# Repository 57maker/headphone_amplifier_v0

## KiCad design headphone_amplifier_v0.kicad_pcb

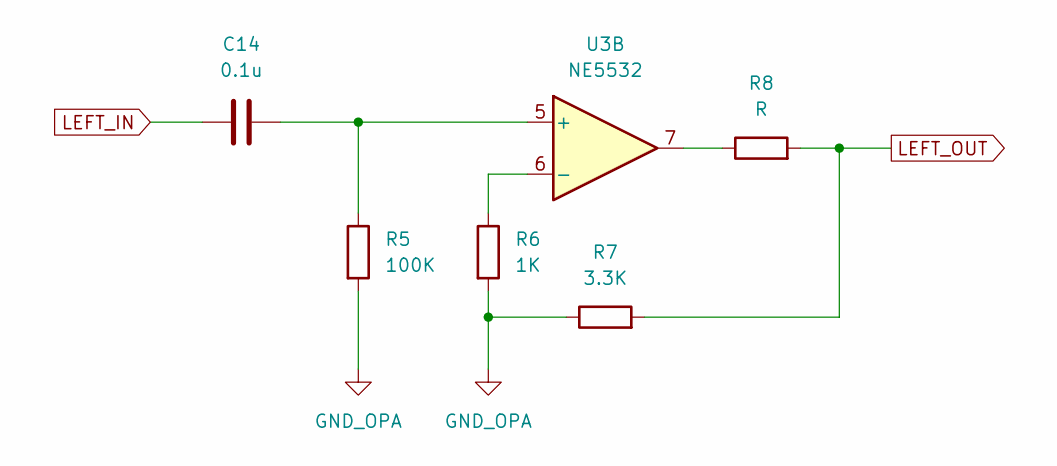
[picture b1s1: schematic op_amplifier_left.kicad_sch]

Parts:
C14: 0.1u; C_Rect_L10.0mm_W5.0mm_P5.00mm_P7.50mm
R5: 100K; R_Axial_DIN0309_L9.0mm_D3.2mm_P12.70mm_Horizontal
R6: 1K; R_Axial_DIN0309_L9.0mm_D3.2mm_P12.70mm_Horizontal
R7: 3.3K; R_Axial_DIN0309_L9.0mm_D3.2mm_P12.70mm_Horizontal
R8: R; R_Axial_DIN0309_L9.0mm_D3.2mm_P12.70mm_Horizontal
U3: NE5532; DIP-8_W7.62mm_Socket

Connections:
GND_OPA: R5.2, R6.2, R7.1; also elsewhere on the board
LEFT_IN: C14.1; also elsewhere on the board
LEFT_OUT: R7.2, R8.2; also elsewhere on the board
unnamed: R8.1, U3.7
unnamed: C14.2, R5.1, U3.5 (+)
unnamed: R6.1, U3.6 (-)

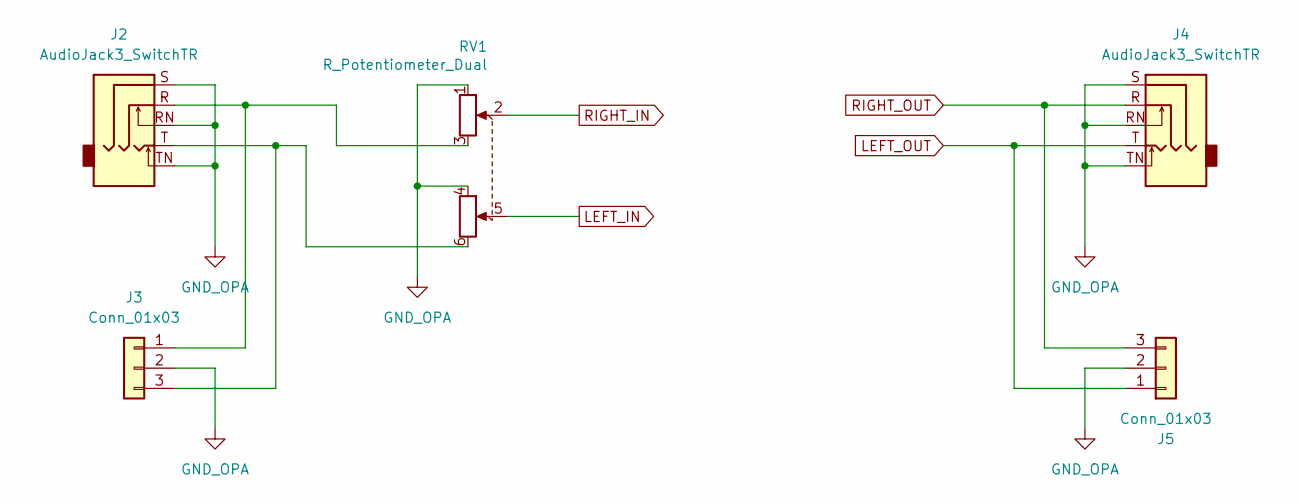
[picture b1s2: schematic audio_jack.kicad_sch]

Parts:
J2, J4: AudioJack3_SwitchTR; Jack_3.5mm_CUI_SJ1-3515N_Horizontal
J3, J5: Conn_01x03; TerminalBlock_TE_282834-3_1x03_P2.54mm_Horizontal
RV1: R_Potentiometer_Dual; Potentiometer_Alps_RK097_Dual_Horizontal

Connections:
GND_OPA: J2.RN, J2.S, J2.TN, J3.2, J4.RN, J4.S, J4.TN, J5.2, RV1.1, RV1.4; also elsewhere on the board
LEFT_IN: RV1.5; also elsewhere on the board
LEFT_OUT: J4.T, J5.1; also elsewhere on the board
unnamed: J2.R, J3.1, RV1.3
unnamed: J2.T, J3.3, RV1.6
RIGHT_IN: RV1.2; also elsewhere on the board
RIGHT_OUT: J4.R, J5.3; also elsewhere on the board

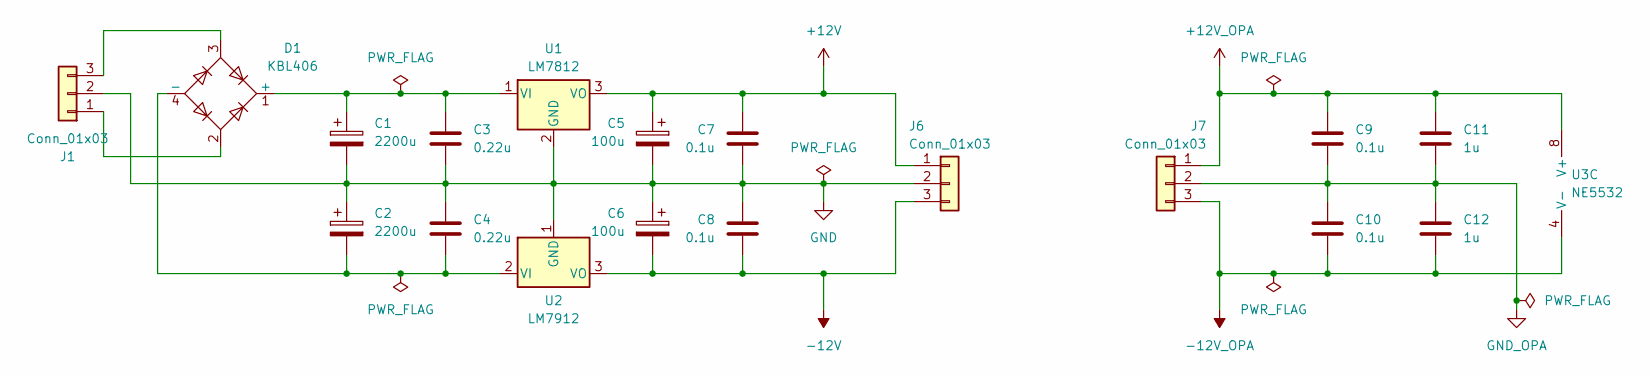
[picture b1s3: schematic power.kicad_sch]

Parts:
C1, C2: 2200u; CP_Radial_D12.5mm_P5.00mm
C3, C4: 0.22u; C_Disc_D5.0mm_W2.5mm_P5.00mm
C5, C6: 100u; CP_Radial_D5.0mm_P2.50mm
C7, C8, C9, C10: 0.1u; C_Disc_D5.0mm_W2.5mm_P5.00mm
C11, C12: 1u; C_Disc_D5.0mm_W2.5mm_P5.00mm
D1: KBL406; Diode_Bridge_Vishay_KBU
J1: Conn_01x03; TerminalBlock_TE_282834-3_1x03_P2.54mm_Horizontal
J6, J7: Conn_01x03; PinHeader_1x03_P2.54mm_Vertical
U1: LM7812; TO-220-3_Vertical
U2: LM7912; TO-220-3_Vertical
U3: NE5532; DIP-8_W7.62mm_Socket

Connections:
+12V: C5.1, C7.2, J6.1, U1.3 (VO)
+12V_OPA: C9.2, C11.2, J7.1, U3.8 (V+)
-12V: C6.2, C8.1, J6.3, U2.3 (VO)
-12V_OPA: C10.1, C12.1, J7.3, U3.4 (V-)
GND: C1.2, C2.1, C3.1, C4.2, C5.2, C6.1, C7.1, C8.2, J1.2, J6.2, U1.2 (GND), U2.1 (GND)
GND_OPA: C9.1, C10.2, C11.1, C12.2, J7.2; also elsewhere on the board
unnamed: C1.1, C3.2, D1.1 (+), U1.1 (VI)
unnamed: C2.2, C4.1, D1.4 (-), U2.2 (VI)
unnamed: D1.2, J1.1
unnamed: D1.3, J1.3

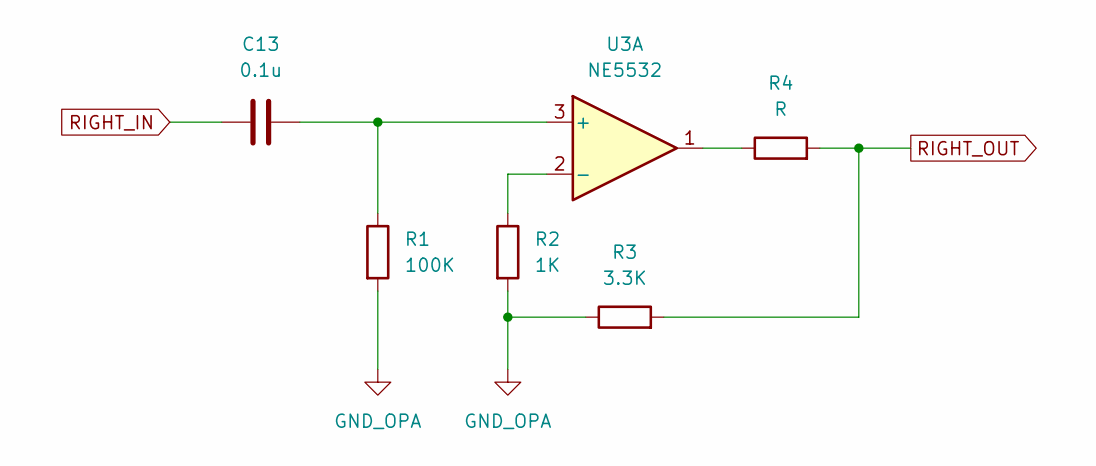
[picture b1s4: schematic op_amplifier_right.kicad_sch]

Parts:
C13: 0.1u; C_Rect_L10.0mm_W5.0mm_P5.00mm_P7.50mm
R1: 100K; R_Axial_DIN0309_L9.0mm_D3.2mm_P12.70mm_Horizontal
R2: 1K; R_Axial_DIN0309_L9.0mm_D3.2mm_P12.70mm_Horizontal
R3: 3.3K; R_Axial_DIN0309_L9.0mm_D3.2mm_P12.70mm_Horizontal
R4: R; R_Axial_DIN0309_L9.0mm_D3.2mm_P12.70mm_Horizontal
U3: NE5532; DIP-8_W7.62mm_Socket

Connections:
GND_OPA: R1.2, R2.2, R3.1; also elsewhere on the board
unnamed: R4.1, U3.1
unnamed: C13.2, R1.1, U3.3 (+)
unnamed: R2.1, U3.2 (-)
RIGHT_IN: C13.1; also elsewhere on the board
RIGHT_OUT: R3.2, R4.2; also elsewhere on the board

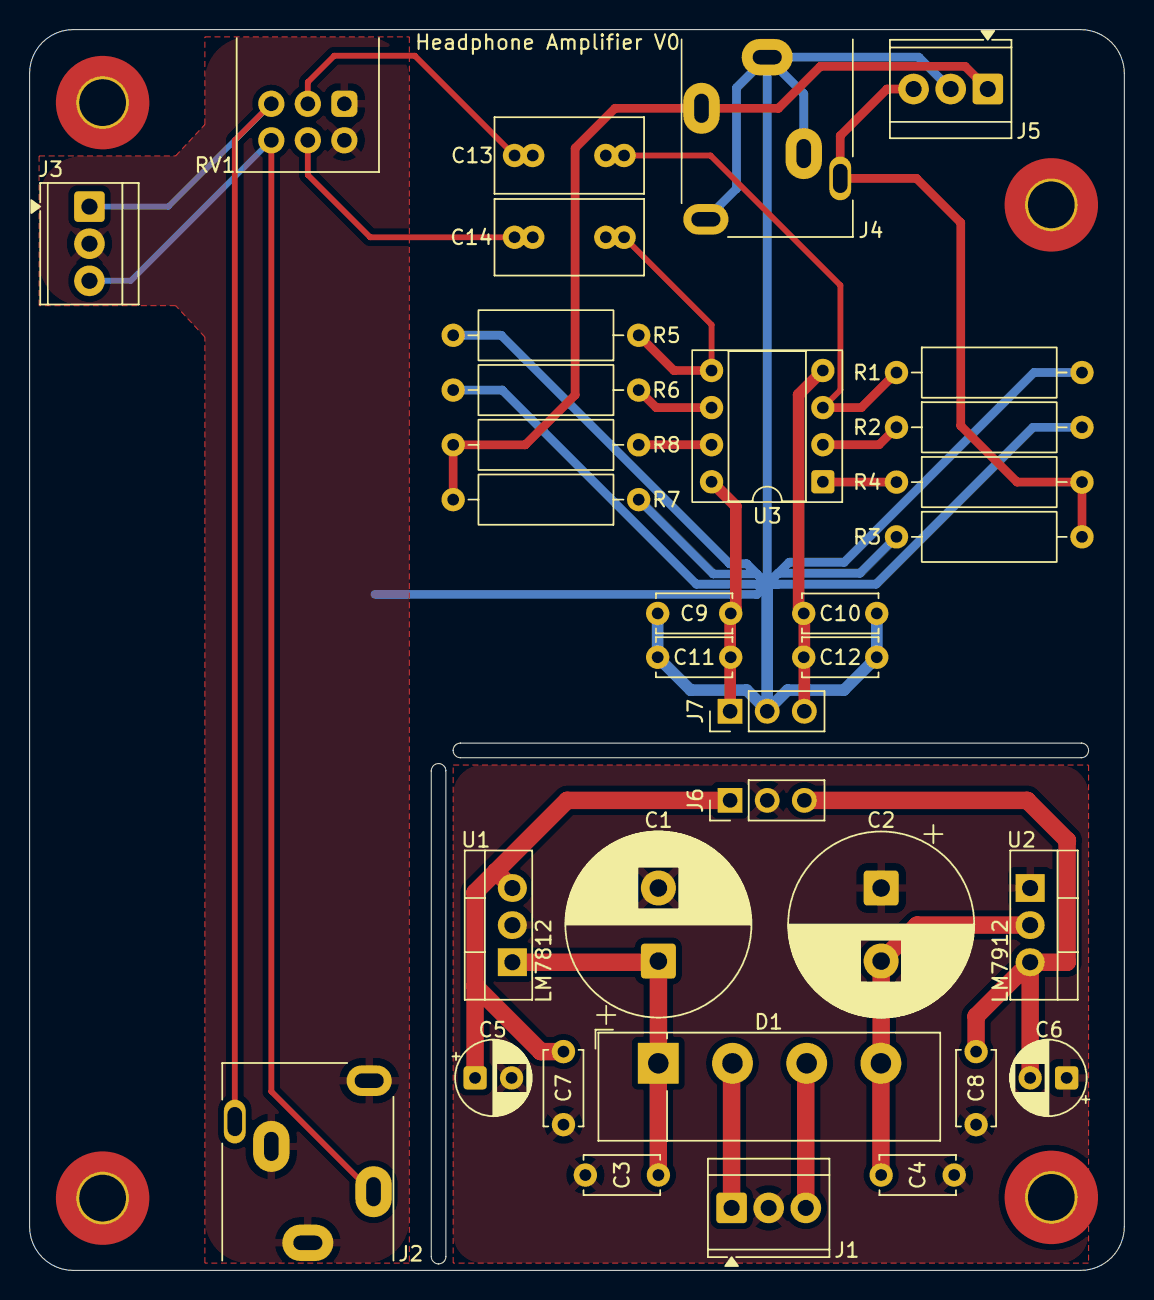
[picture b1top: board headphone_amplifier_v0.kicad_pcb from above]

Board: 2 copper layers, 74.9 x 84.9 mm, 34 parts (0 on the bottom side), 22 nets.

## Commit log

2025-11-10 implement function modules
2025-11-17 complete layout
2025-11-17 revise layout change footprint of RK097 dual
